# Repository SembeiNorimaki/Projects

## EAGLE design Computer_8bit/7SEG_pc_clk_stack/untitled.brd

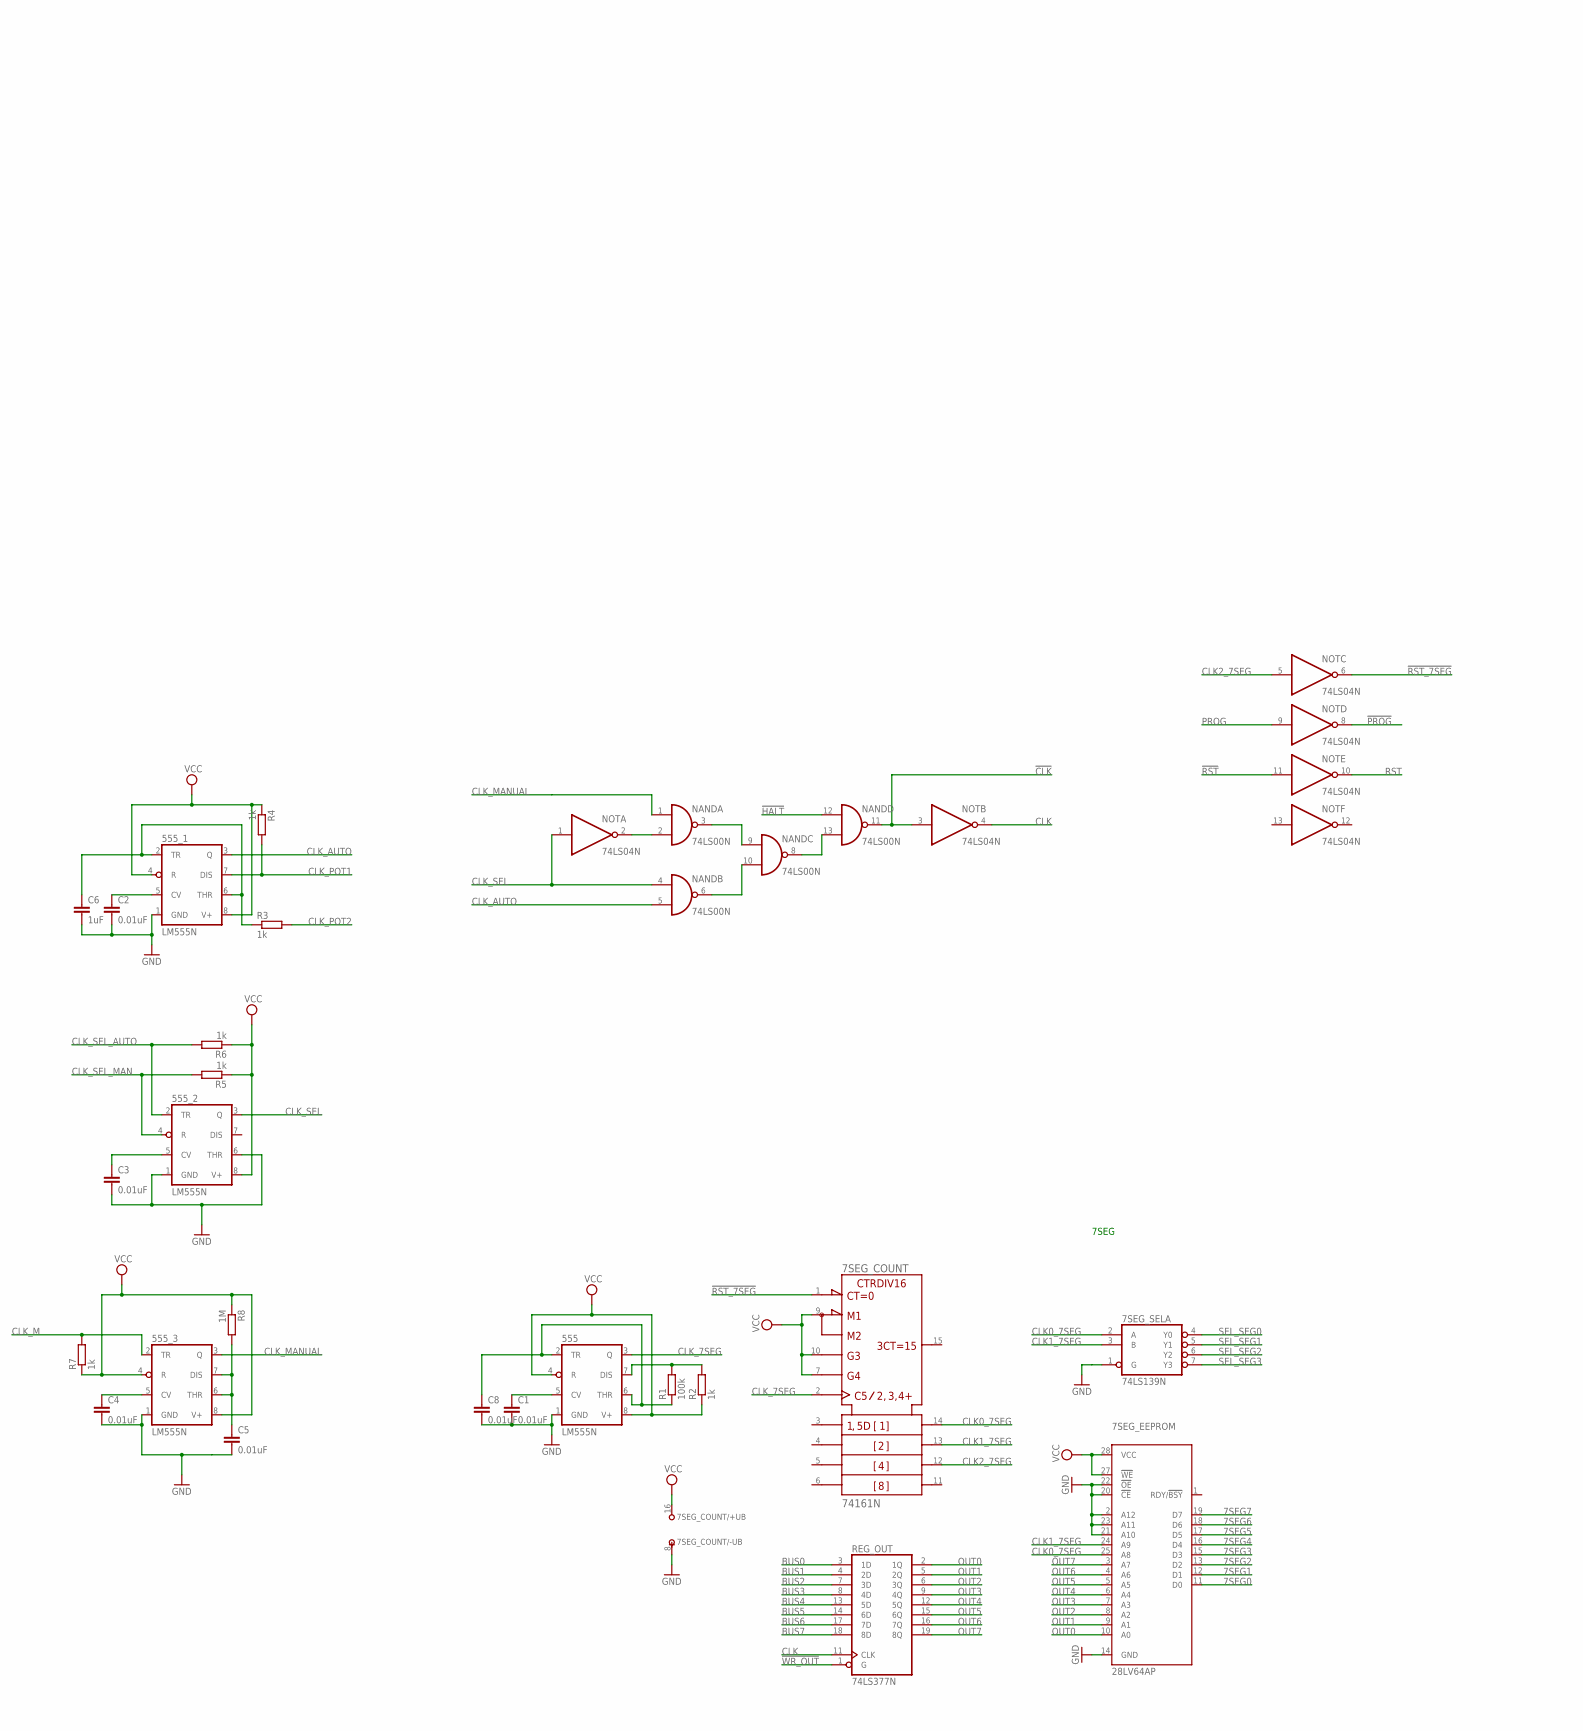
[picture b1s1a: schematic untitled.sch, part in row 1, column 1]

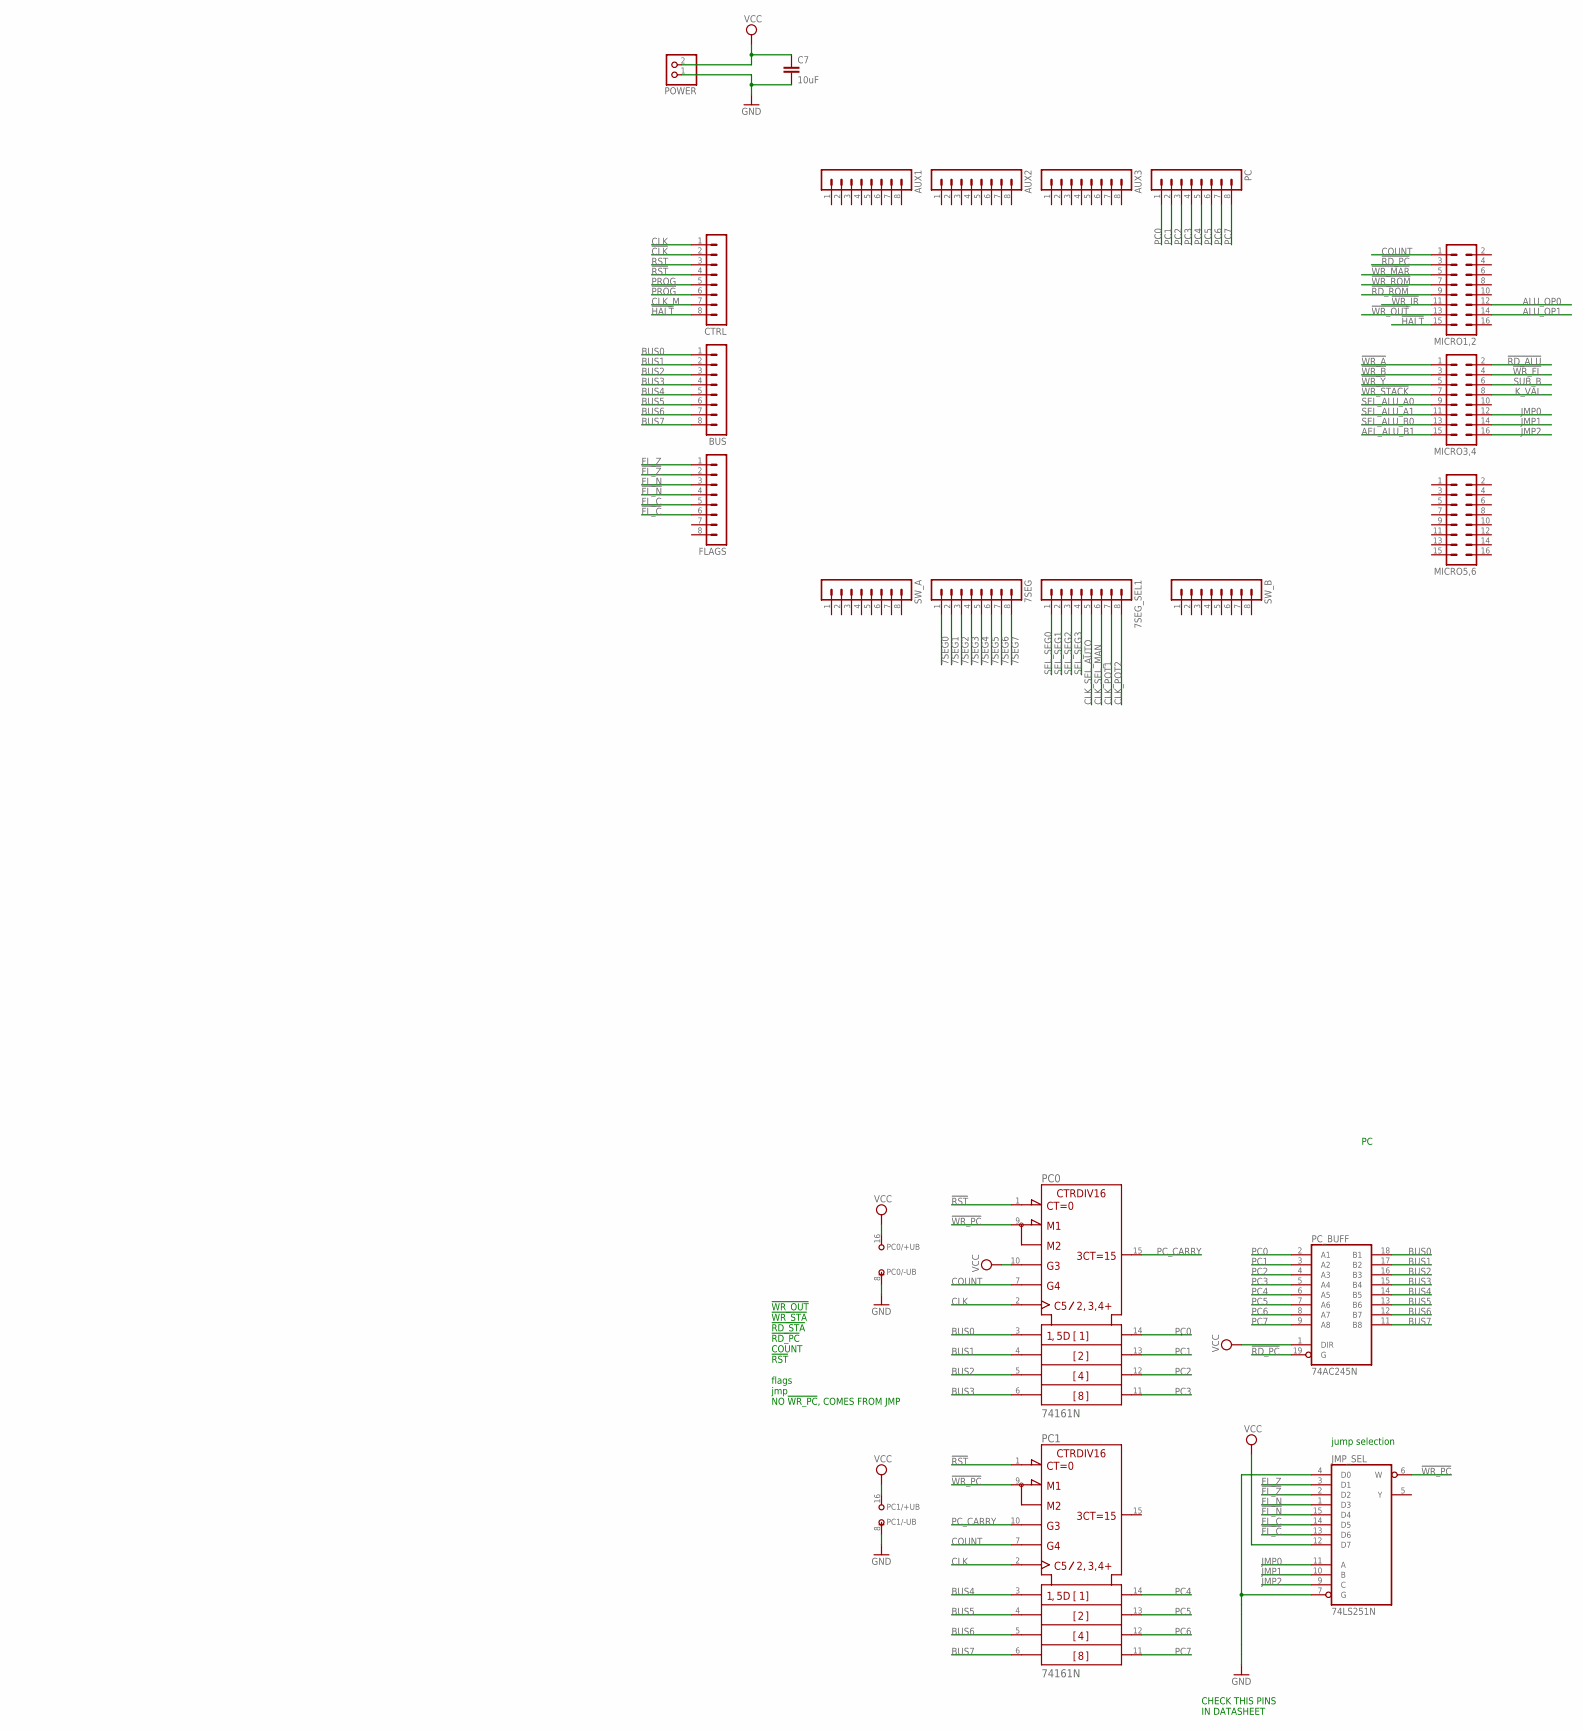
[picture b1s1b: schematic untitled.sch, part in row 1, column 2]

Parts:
7SEG, 7SEG_SEL1: MA08-1
7SEG_COUNT: 74161N; DIL16
7SEG_EEPROM: 28LV64AP; DIL28-6
7SEG_SEL: 74LS139N; DIL16
555, 555_1, 555_2, 555_3: LM555N; DIL08
AUX1, AUX2, AUX3: MA08-1
BUS: MA08-1
C1, C2, C3, C4, C5, C8: 0.01uF; C2.5-2
C6: 1uF; C2.5-2
C7: 10uF; C025-050X050
CTRL: MA08-1
FLAGS: MA08-1
JMP_SEL: 74LS251N; DIL16
MICRO1,2, MICRO3,4, MICRO5,6: MA08-2
NAND: 74LS00N; DIL14
NOT: 74LS04N; DIL14
PC: MA08-1
PC0, PC1: 74161N; DIL16
PC_BUFF: 74AC245N; DIL20
POWER: PINHD-1X2; 1X02
R1: 100k; 0207/10
R2, R3, R4, R5, R6, R7: 1k; 0207/10
R8: 1M; 0207/10
REG_OUT: 74LS377N; DIL20
SW_A: MA08-1
SW_B: MA08-1

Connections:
7SEG0: 7SEG.1, 7SEG_EEPROM.11 (D0)
7SEG1: 7SEG.2, 7SEG_EEPROM.12 (D1)
7SEG2: 7SEG.3, 7SEG_EEPROM.13 (D2)
7SEG3: 7SEG.4, 7SEG_EEPROM.15 (D3)
7SEG4: 7SEG.5, 7SEG_EEPROM.16 (D4)
7SEG5: 7SEG.6, 7SEG_EEPROM.17 (D5)
7SEG6: 7SEG.7, 7SEG_EEPROM.18 (D6)
7SEG7: 7SEG.8, 7SEG_EEPROM.19 (D7)
!CLK: CTRL.2, NAND.11 (O), NOT.3 (I)
!FL_C: FLAGS.6, JMP_SEL.13 (D6)
!FL_N: FLAGS.4, JMP_SEL.15 (D4)
!FL_Z: FLAGS.2, JMP_SEL.2 (D2)
!HALT: CTRL.8, MICRO1,2.15, NAND.12 (I0)
!PROG: CTRL.6, NOT.8 (O)
!RD_ALU: MICRO3,4.2
!RD_PC: MICRO1,2.3, PC_BUFF.19 (G)
!RD_ROM: MICRO1,2.9
!RST: CTRL.4, NOT.11 (I), PC0.1 (!CLR), PC1.1 (!CLR)
!RST_7SEG: 7SEG_COUNT.1 (!CLR), NOT.6 (O)
!WR_A: MICRO3,4.1
!WR_B: MICRO3,4.3
!WR_FL: MICRO3,4.4
!WR_IR: MICRO1,2.11
!WR_MAR: MICRO1,2.5
!WR_OUT: MICRO1,2.13, REG_OUT.1 (G)
!WR_PC: JMP_SEL.6 (W), PC0.9 (!LOAD), PC1.9 (!LOAD)
!WR_ROM: MICRO1,2.7
!WR_STACK: MICRO3,4.7
!WR_Y: MICRO3,4.5
AEL_ALU_B1: MICRO3,4.15
ALU_OP0: MICRO1,2.12
ALU_OP1: MICRO1,2.14
BUS0: BUS.1, PC0.3 (A), PC_BUFF.18 (B1), REG_OUT.3 (1D)
BUS1: BUS.2, PC0.4 (B), PC_BUFF.17 (B2), REG_OUT.4 (2D)
BUS2: BUS.3, PC0.5 (C), PC_BUFF.16 (B3), REG_OUT.7 (3D)
BUS3: BUS.4, PC0.6 (D), PC_BUFF.15 (B4), REG_OUT.8 (4D)
BUS4: BUS.5, PC1.3 (A), PC_BUFF.14 (B5), REG_OUT.13 (5D)
BUS5: BUS.6, PC1.4 (B), PC_BUFF.13 (B6), REG_OUT.14 (6D)
BUS6: BUS.7, PC1.5 (C), PC_BUFF.12 (B7), REG_OUT.17 (7D)
BUS7: BUS.8, PC1.6 (D), PC_BUFF.11 (B8), REG_OUT.18 (8D)
CLK: CTRL.1, NOT.4 (O), PC0.2 (CLK), PC1.2 (CLK), REG_OUT.11 (CLK)
CLK0_7SEG: 7SEG_COUNT.14 (QA), 7SEG_EEPROM.25 (A8), 7SEG_SEL.2 (A)
CLK1_7SEG: 7SEG_COUNT.13 (QB), 7SEG_EEPROM.24 (A9), 7SEG_SEL.3 (B)
CLK2_7SEG: 7SEG_COUNT.12 (QC), NOT.5 (I)
CLK_7SEG: 7SEG_COUNT.2 (CLK), 555.3 (Q)
CLK_AUTO: 555_1.3 (Q), NAND.5 (I1)
CLK_M: 555_3.2 (TR), CTRL.7, R7.2
CLK_MANUAL: 555_3.3 (Q), NAND.1 (I0)
CLK_POT1: 7SEG_SEL1.7, 555_1.7 (DIS), R4.2
CLK_POT2: 7SEG_SEL1.8, R3.2
CLK_SEL: 555_2.3 (Q), NAND.4 (I0), NOT.1 (I)
CLK_SEL_AUTO: 7SEG_SEL1.5, 555_2.2 (TR), R6.2
CLK_SEL_MAN: 7SEG_SEL1.6, 555_2.4 (R), R5.2
COUNT: MICRO1,2.1, PC0.7 (ENP), PC1.7 (ENP)
FL_C: FLAGS.5, JMP_SEL.14 (D5)
FL_N: FLAGS.3, JMP_SEL.1 (D3)
FL_Z: FLAGS.1, JMP_SEL.3 (D1)
GND: 7SEG_COUNT.8 (-UB), 7SEG_EEPROM.2 (A12), 7SEG_EEPROM.14 (GND), 7SEG_EEPROM.20 (!CE), 7SEG_EEPROM.21 (A10), 7SEG_EEPROM.22 (!OE), 7SEG_EEPROM.23 (A11), 7SEG_SEL.1 (G), 7SEG_SEL.8 (GND), 555.1 (GND), 555_1.1 (GND), 555_2.1 (GND), 555_2.6 (THR), 555_3.1 (GND), C1.2, C2.2, C3.2, C4.2, C5.2, C6.2, C7.2, C8.2, JMP_SEL.4 (D0), JMP_SEL.7 (G), JMP_SEL.8 (GND), NAND.7 (GND), NOT.7 (GND), PC0.8 (-UB), PC1.8 (-UB), PC_BUFF.10 (GND), POWER.1, REG_OUT.10 (GND)
JMP0: JMP_SEL.11 (A), MICRO3,4.12
JMP1: JMP_SEL.10 (B), MICRO3,4.14
JMP2: JMP_SEL.9 (C), MICRO3,4.16
K_VAL: MICRO3,4.8
unnamed: 555_2.5 (CV), C3.1
unnamed: 555_1.5 (CV), C2.1
unnamed: NAND.3 (O), NAND.9 (I0)
unnamed: 555_1.2 (TR), 555_1.6 (THR), C6.1, R3.1
unnamed: 555_3.5 (CV), C4.1
unnamed: 555.7 (DIS), R1.2, R2.2
unnamed: 555.5 (CV), C1.1
unnamed: 555.2 (TR), 555.6 (THR), C8.1, R1.1
unnamed: 555_3.6 (THR), 555_3.7 (DIS), C5.1, R8.2
unnamed: NAND.6 (O), NAND.10 (I1)
unnamed: NAND.8 (O), NAND.13 (I1)
unnamed: NAND.2 (I1), NOT.2 (O)
OUT0: 7SEG_EEPROM.10 (A0), REG_OUT.2 (1Q)
OUT1: 7SEG_EEPROM.9 (A1), REG_OUT.5 (2Q)
OUT2: 7SEG_EEPROM.8 (A2), REG_OUT.6 (3Q)
OUT3: 7SEG_EEPROM.7 (A3), REG_OUT.9 (4Q)
OUT4: 7SEG_EEPROM.6 (A4), REG_OUT.12 (5Q)
OUT5: 7SEG_EEPROM.5 (A5), REG_OUT.15 (6Q)
OUT6: 7SEG_EEPROM.4 (A6), REG_OUT.16 (7Q)
OUT7: 7SEG_EEPROM.3 (A7), REG_OUT.19 (8Q)
PC0: PC.1, PC0.14 (QA), PC_BUFF.2 (A1)
PC1: PC.2, PC0.13 (QB), PC_BUFF.3 (A2)
PC2: PC.3, PC0.12 (QC), PC_BUFF.4 (A3)
PC3: PC.4, PC0.11 (QD), PC_BUFF.5 (A4)
PC4: PC.5, PC1.14 (QA), PC_BUFF.6 (A5)
PC5: PC.6, PC1.13 (QB), PC_BUFF.7 (A6)
PC6: PC.7, PC1.12 (QC), PC_BUFF.8 (A7)
PC7: PC.8, PC1.11 (QD), PC_BUFF.9 (A8)
PC_CARRY: PC0.15 (RCO), PC1.10 (ENT)
PROG: CTRL.5, NOT.9 (I)
RST: CTRL.3, NOT.10 (O)
SEL_ALU_A0: MICRO3,4.9
SEL_ALU_A1: MICRO3,4.11
SEL_ALU_B0: MICRO3,4.13
SEL_SEG0: 7SEG_SEL.4 (Y0), 7SEG_SEL1.1
SEL_SEG1: 7SEG_SEL.5 (Y1), 7SEG_SEL1.2
SEL_SEG2: 7SEG_SEL.6 (Y2), 7SEG_SEL1.3
SEL_SEG3: 7SEG_SEL.7 (Y3), 7SEG_SEL1.4
SUB_B: MICRO3,4.6
VCC: 7SEG_COUNT.7 (ENP), 7SEG_COUNT.9 (!LOAD), 7SEG_COUNT.10 (ENT), 7SEG_COUNT.16 (+UB), 7SEG_EEPROM.27 (!WE), 7SEG_EEPROM.28 (VCC), 7SEG_SEL.16 (VCC), 555.4 (R), 555.8 (V+), 555_1.4 (R), 555_1.8 (V+), 555_2.8 (V+), 555_3.4 (R), 555_3.8 (V+), C7.1, JMP_SEL.12 (D7), JMP_SEL.16 (VCC), NAND.14 (VCC), NOT.14 (VCC), PC0.10 (ENT), PC0.16 (+UB), PC1.16 (+UB), PC_BUFF.1 (DIR), PC_BUFF.20 (VCC), POWER.2, R2.1, R4.1, R5.1, R6.1, R7.1, R8.1, REG_OUT.20 (VCC)

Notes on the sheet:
jump selection
CHECK THIS PINS IN DATASHEET
!WR_OUT !WR_STA !RD_STA !RD_PC COUNT !RST flags jmp NO !WR_PC, COMES FROM JMP
7SEG

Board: 2 copper layers, 45 parts (0 on the bottom side), 84 nets, no tracks yet.

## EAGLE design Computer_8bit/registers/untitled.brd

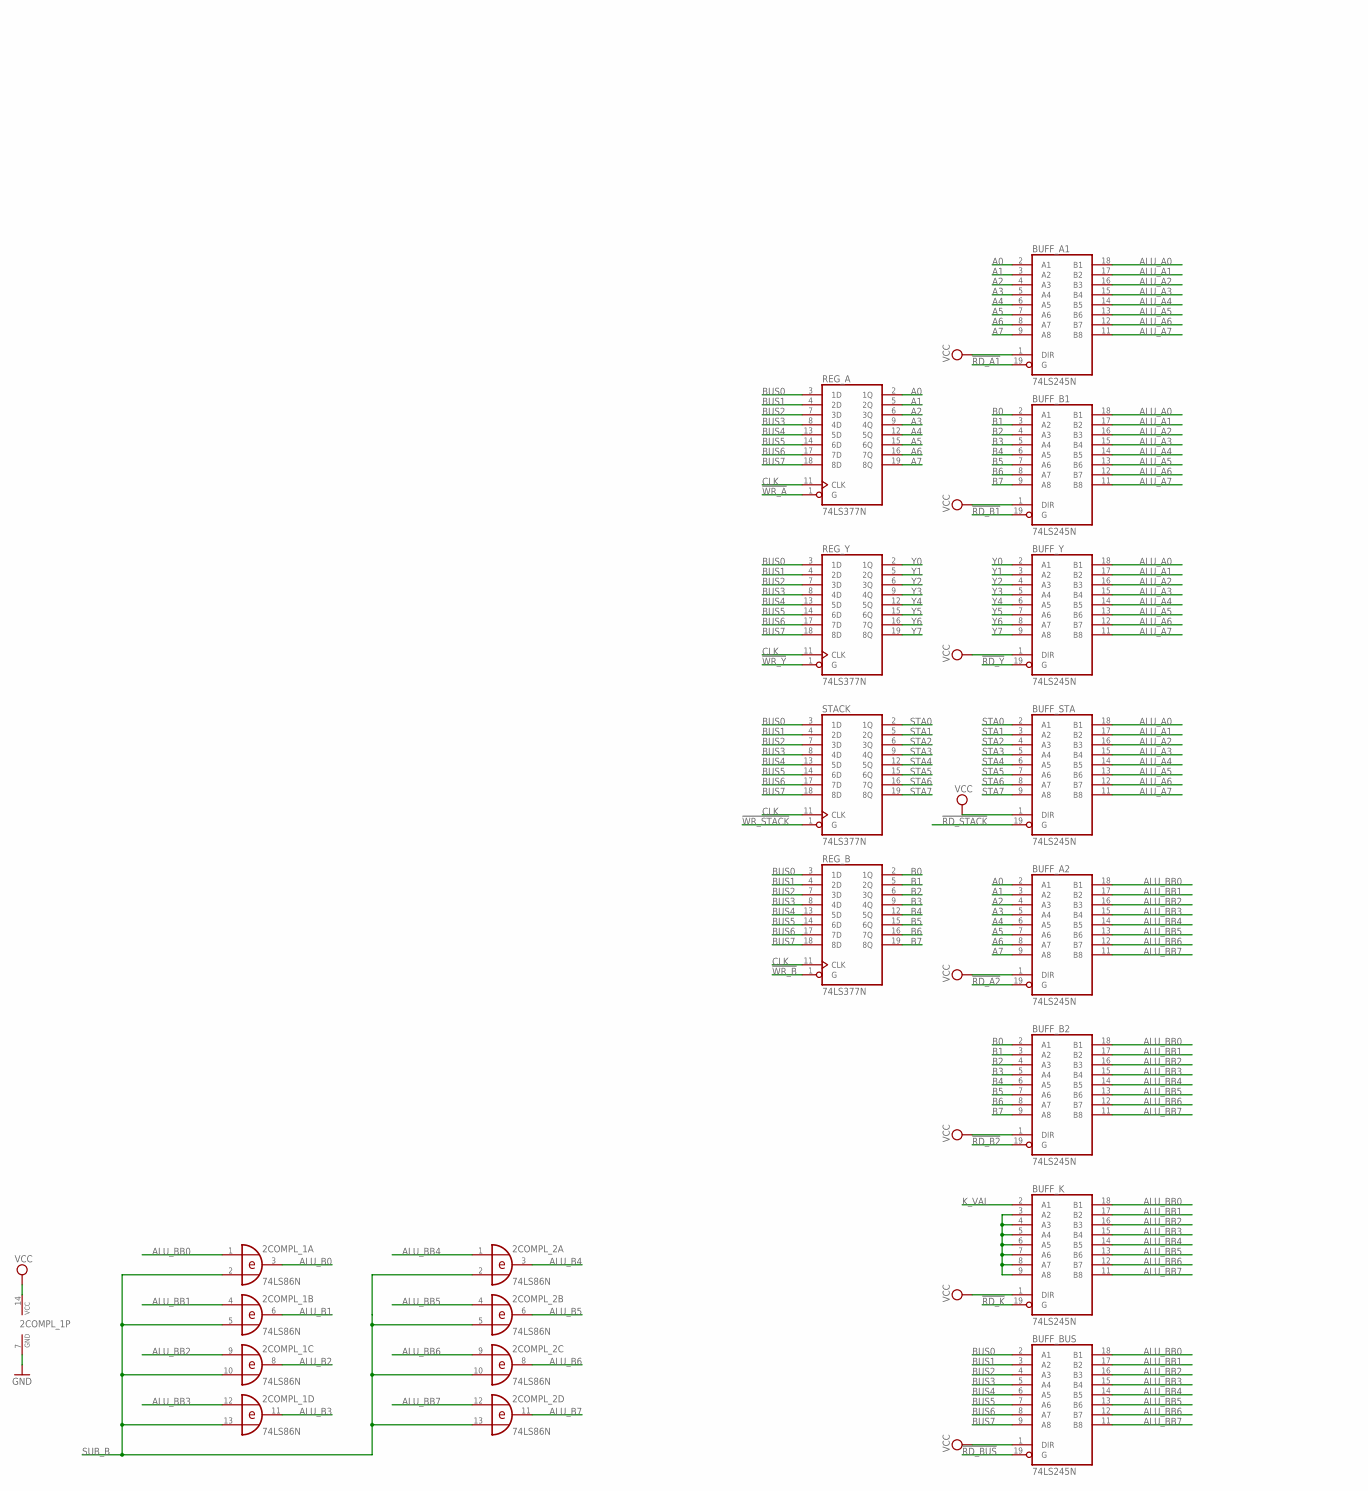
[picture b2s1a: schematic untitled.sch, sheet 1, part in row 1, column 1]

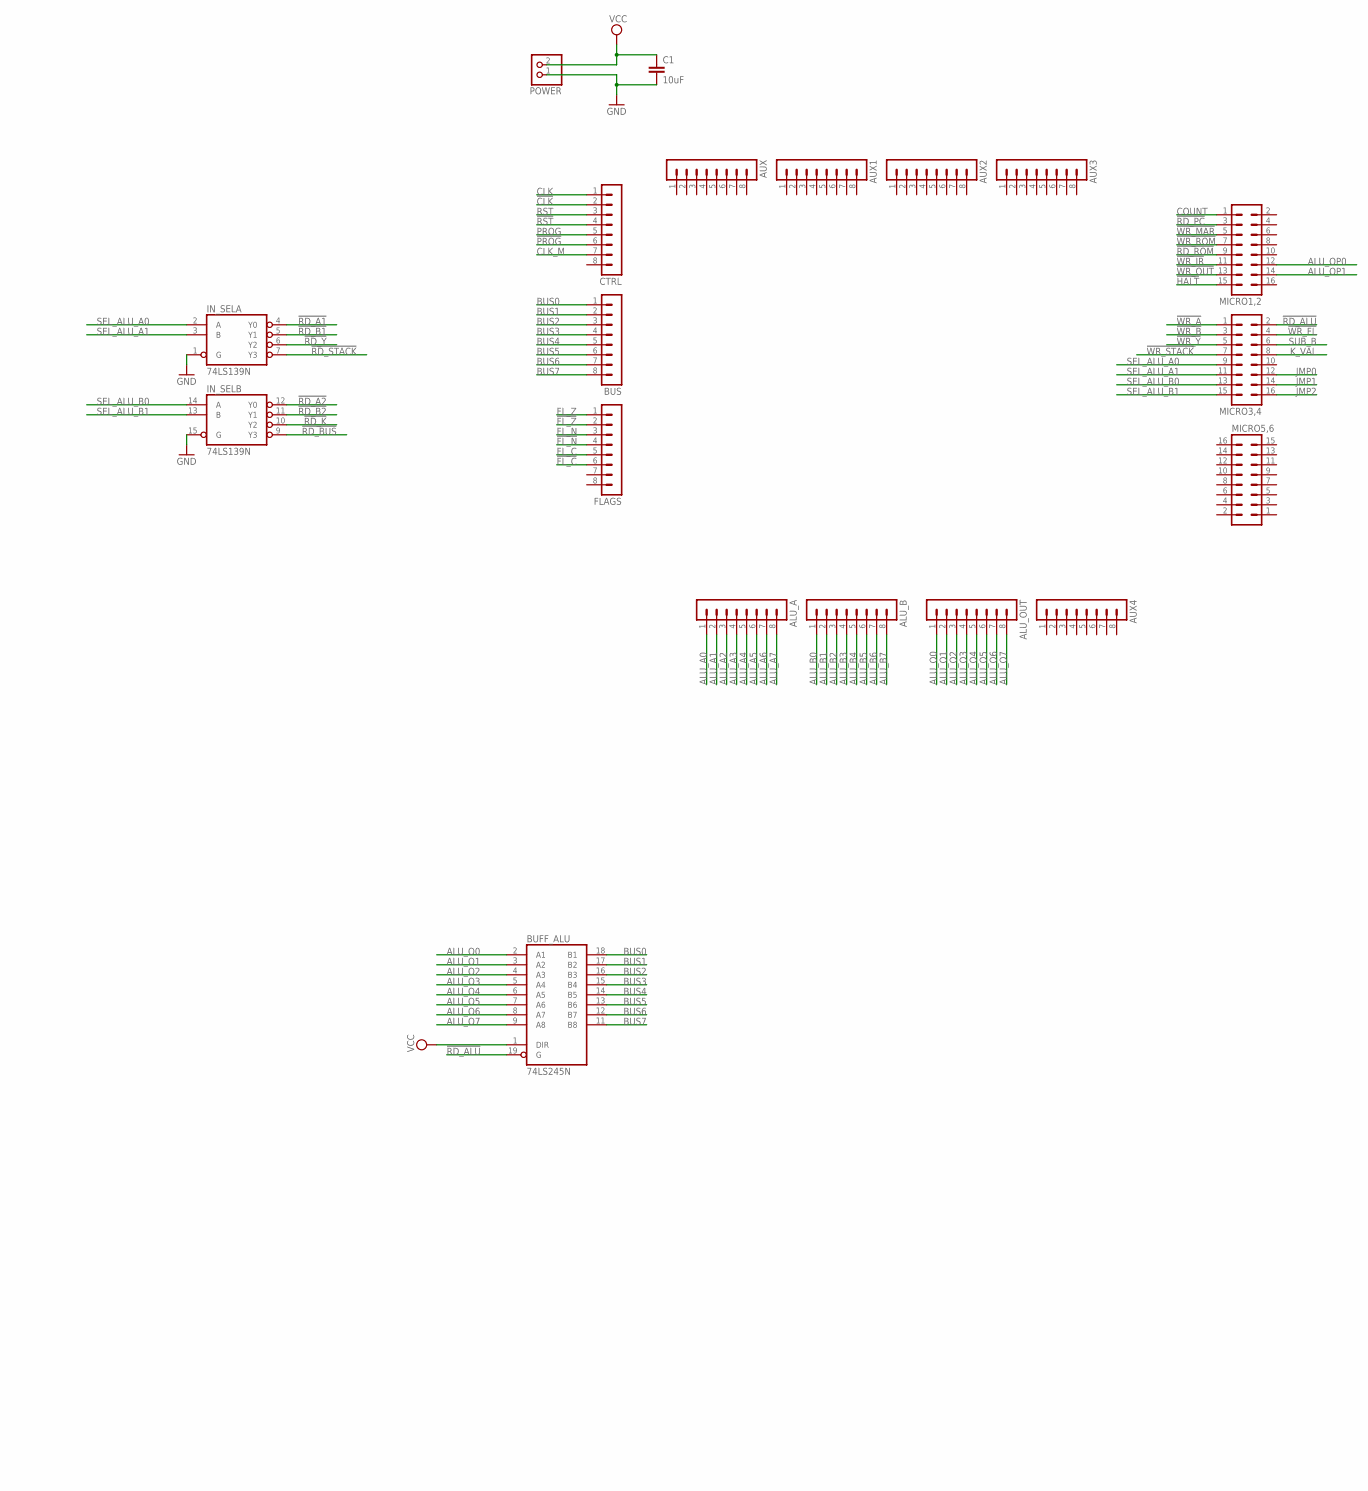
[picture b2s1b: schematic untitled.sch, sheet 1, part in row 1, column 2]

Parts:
2COMPL_1, 2COMPL_2: 74LS86N; DIL14
ALU_A: MA08-1
ALU_B: MA08-1
ALU_OUT: MA08-1
AUX, AUX1, AUX2, AUX3, AUX4: MA08-1
BUFF_A1, BUFF_A2: 74LS245N; DIL20
BUFF_ALU: 74LS245N; DIL20
BUFF_B1, BUFF_B2: 74LS245N; DIL20
BUFF_BUS: 74LS245N; DIL20
BUFF_K: 74LS245N; DIL20
BUFF_STA: 74LS245N; DIL20
BUFF_Y: 74LS245N; DIL20
BUS: MA08-1
C1: 10uF; C025-050X050
CTRL: MA08-1
FLAGS: MA08-1
IN_SEL: 74LS139N; DIL16
MICRO1,2, MICRO3,4, MICRO5,6: MA08-2
POWER: PINHD-1X2; 1X02
REG_A: 74LS377N; DIL20
REG_B: 74LS377N; DIL20
REG_Y: 74LS377N; DIL20
STACK: 74LS377N; DIL20

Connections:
!CLK: CTRL.2
!FL_C: FLAGS.6
!FL_N: FLAGS.4
!FL_Z: FLAGS.2
!HALT: MICRO1,2.15
!PROG: CTRL.6
!RD_A1: BUFF_A1.19 (G), IN_SEL.4 (Y0)
!RD_A2: BUFF_A2.19 (G), IN_SEL.12 (Y0)
!RD_ALU: BUFF_ALU.19 (G), MICRO3,4.2
!RD_B1: BUFF_B1.19 (G), IN_SEL.5 (Y1)
!RD_B2: BUFF_B2.19 (G), IN_SEL.11 (Y1)
!RD_BUS: BUFF_BUS.19 (G), IN_SEL.9 (Y3)
!RD_K: BUFF_K.19 (G), IN_SEL.10 (Y2)
!RD_PC: MICRO1,2.3
!RD_ROM: MICRO1,2.9
!RD_STACK: BUFF_STA.19 (G), IN_SEL.7 (Y3)
!RD_Y: BUFF_Y.19 (G), IN_SEL.6 (Y2)
!RST: CTRL.4
!WR_A: MICRO3,4.1, REG_A.1 (G)
!WR_B: MICRO3,4.3, REG_B.1 (G)
!WR_FL: MICRO3,4.4
!WR_IR: MICRO1,2.11
!WR_MAR: MICRO1,2.5
!WR_OUT: MICRO1,2.13
!WR_ROM: MICRO1,2.7
!WR_STACK: MICRO3,4.7, STACK.1 (G)
!WR_Y: MICRO3,4.5, REG_Y.1 (G)
A0: BUFF_A1.2 (A1), BUFF_A2.2 (A1), REG_A.2 (1Q)
A1: BUFF_A1.3 (A2), BUFF_A2.3 (A2), REG_A.5 (2Q)
A2: BUFF_A1.4 (A3), BUFF_A2.4 (A3), REG_A.6 (3Q)
A3: BUFF_A1.5 (A4), BUFF_A2.5 (A4), REG_A.9 (4Q)
A4: BUFF_A1.6 (A5), BUFF_A2.6 (A5), REG_A.12 (5Q)
A5: BUFF_A1.7 (A6), BUFF_A2.7 (A6), REG_A.15 (6Q)
A6: BUFF_A1.8 (A7), BUFF_A2.8 (A7), REG_A.16 (7Q)
A7: BUFF_A1.9 (A8), BUFF_A2.9 (A8), REG_A.19 (8Q)
ALU_A0: ALU_A.1, BUFF_A1.18 (B1), BUFF_B1.18 (B1), BUFF_STA.18 (B1), BUFF_Y.18 (B1)
ALU_A1: ALU_A.2, BUFF_A1.17 (B2), BUFF_B1.17 (B2), BUFF_STA.17 (B2), BUFF_Y.17 (B2)
ALU_A2: ALU_A.3, BUFF_A1.16 (B3), BUFF_B1.16 (B3), BUFF_STA.16 (B3), BUFF_Y.16 (B3)
ALU_A3: ALU_A.4, BUFF_A1.15 (B4), BUFF_B1.15 (B4), BUFF_STA.15 (B4), BUFF_Y.15 (B4)
ALU_A4: ALU_A.5, BUFF_A1.14 (B5), BUFF_B1.14 (B5), BUFF_STA.14 (B5), BUFF_Y.14 (B5)
ALU_A5: ALU_A.6, BUFF_A1.13 (B6), BUFF_B1.13 (B6), BUFF_STA.13 (B6), BUFF_Y.13 (B6)
ALU_A6: ALU_A.7, BUFF_A1.12 (B7), BUFF_B1.12 (B7), BUFF_STA.12 (B7), BUFF_Y.12 (B7)
ALU_A7: ALU_A.8, BUFF_A1.11 (B8), BUFF_B1.11 (B8), BUFF_STA.11 (B8), BUFF_Y.11 (B8)
ALU_B0: 2COMPL_1.3 (O), ALU_B.1
ALU_B1: 2COMPL_1.6 (O), ALU_B.2
ALU_B2: 2COMPL_1.8 (O), ALU_B.3
ALU_B3: 2COMPL_1.11 (O), ALU_B.4
ALU_B4: 2COMPL_2.3 (O), ALU_B.5
ALU_B5: 2COMPL_2.6 (O), ALU_B.6
ALU_B6: 2COMPL_2.8 (O), ALU_B.7
ALU_B7: 2COMPL_2.11 (O), ALU_B.8
ALU_BB0: 2COMPL_1.1 (I0), BUFF_A2.18 (B1), BUFF_B2.18 (B1), BUFF_BUS.18 (B1), BUFF_K.18 (B1)
ALU_BB1: 2COMPL_1.4 (I0), BUFF_A2.17 (B2), BUFF_B2.17 (B2), BUFF_BUS.17 (B2), BUFF_K.17 (B2)
ALU_BB2: 2COMPL_1.9 (I0), BUFF_A2.16 (B3), BUFF_B2.16 (B3), BUFF_BUS.16 (B3), BUFF_K.16 (B3)
ALU_BB3: 2COMPL_1.12 (I0), BUFF_A2.15 (B4), BUFF_B2.15 (B4), BUFF_BUS.15 (B4), BUFF_K.15 (B4)
ALU_BB4: 2COMPL_2.1 (I0), BUFF_A2.14 (B5), BUFF_B2.14 (B5), BUFF_BUS.14 (B5), BUFF_K.14 (B5)
ALU_BB5: 2COMPL_2.4 (I0), BUFF_A2.13 (B6), BUFF_B2.13 (B6), BUFF_BUS.13 (B6), BUFF_K.13 (B6)
ALU_BB6: 2COMPL_2.9 (I0), BUFF_A2.12 (B7), BUFF_B2.12 (B7), BUFF_BUS.12 (B7), BUFF_K.12 (B7)
ALU_BB7: 2COMPL_2.12 (I0), BUFF_A2.11 (B8), BUFF_B2.11 (B8), BUFF_BUS.11 (B8), BUFF_K.11 (B8)
ALU_O0: ALU_OUT.1, BUFF_ALU.2 (A1)
ALU_O1: ALU_OUT.2, BUFF_ALU.3 (A2)
ALU_O2: ALU_OUT.3, BUFF_ALU.4 (A3)
ALU_O3: ALU_OUT.4, BUFF_ALU.5 (A4)
ALU_O4: ALU_OUT.5, BUFF_ALU.6 (A5)
ALU_O5: ALU_OUT.6, BUFF_ALU.7 (A6)
ALU_O6: ALU_OUT.7, BUFF_ALU.8 (A7)
ALU_O7: ALU_OUT.8, BUFF_ALU.9 (A8)
ALU_OP0: MICRO1,2.12
ALU_OP1: MICRO1,2.14
B0: BUFF_B1.2 (A1), BUFF_B2.2 (A1), REG_B.2 (1Q)
B1: BUFF_B1.3 (A2), BUFF_B2.3 (A2), REG_B.5 (2Q)
B2: BUFF_B1.4 (A3), BUFF_B2.4 (A3), REG_B.6 (3Q)
B3: BUFF_B1.5 (A4), BUFF_B2.5 (A4), REG_B.9 (4Q)
B4: BUFF_B1.6 (A5), BUFF_B2.6 (A5), REG_B.12 (5Q)
B5: BUFF_B1.7 (A6), BUFF_B2.7 (A6), REG_B.15 (6Q)
B6: BUFF_B1.8 (A7), BUFF_B2.8 (A7), REG_B.16 (7Q)
B7: BUFF_B1.9 (A8), BUFF_B2.9 (A8), REG_B.19 (8Q)
BUS0: BUFF_ALU.18 (B1), BUFF_BUS.2 (A1), BUS.1, REG_A.3 (1D), REG_B.3 (1D), REG_Y.3 (1D), STACK.3 (1D)
BUS1: BUFF_ALU.17 (B2), BUFF_BUS.3 (A2), BUS.2, REG_A.4 (2D), REG_B.4 (2D), REG_Y.4 (2D), STACK.4 (2D)
BUS2: BUFF_ALU.16 (B3), BUFF_BUS.4 (A3), BUS.3, REG_A.7 (3D), REG_B.7 (3D), REG_Y.7 (3D), STACK.7 (3D)
BUS3: BUFF_ALU.15 (B4), BUFF_BUS.5 (A4), BUS.4, REG_A.8 (4D), REG_B.8 (4D), REG_Y.8 (4D), STACK.8 (4D)
BUS4: BUFF_ALU.14 (B5), BUFF_BUS.6 (A5), BUS.5, REG_A.13 (5D), REG_B.13 (5D), REG_Y.13 (5D), STACK.13 (5D)
BUS5: BUFF_ALU.13 (B6), BUFF_BUS.7 (A6), BUS.6, REG_A.14 (6D), REG_B.14 (6D), REG_Y.14 (6D), STACK.14 (6D)
BUS6: BUFF_ALU.12 (B7), BUFF_BUS.8 (A7), BUS.7, REG_A.17 (7D), REG_B.17 (7D), REG_Y.17 (7D), STACK.17 (7D)
BUS7: BUFF_ALU.11 (B8), BUFF_BUS.9 (A8), BUS.8, REG_A.18 (8D), REG_B.18 (8D), REG_Y.18 (8D), STACK.18 (8D)
CLK: CTRL.1, REG_A.11 (CLK), REG_B.11 (CLK), REG_Y.11 (CLK), STACK.11 (CLK)
CLK_M: CTRL.7
COUNT: MICRO1,2.1
FL_C: FLAGS.5
FL_N: FLAGS.3
FL_Z: FLAGS.1
GND: 2COMPL_1.7 (GND), 2COMPL_2.7 (GND), BUFF_A1.10 (GND), BUFF_A2.10 (GND), BUFF_ALU.10 (GND), BUFF_B1.10 (GND), BUFF_B2.10 (GND), BUFF_BUS.10 (GND), BUFF_K.10 (GND), BUFF_STA.10 (GND), BUFF_Y.10 (GND), C1.2, IN_SEL.1 (G), IN_SEL.8 (GND), IN_SEL.15 (G), POWER.1, REG_A.10 (GND), REG_B.10 (GND), REG_Y.10 (GND), STACK.10 (GND)
JMP0: MICRO3,4.12
JMP1: MICRO3,4.14
JMP2: MICRO3,4.16
K_VAL: BUFF_K.2 (A1), MICRO3,4.8
unnamed: BUFF_K.3 (A2), BUFF_K.4 (A3), BUFF_K.5 (A4), BUFF_K.6 (A5), BUFF_K.7 (A6), BUFF_K.8 (A7), BUFF_K.9 (A8)
PROG: CTRL.5
RST: CTRL.3
SEL_ALU_A0: IN_SEL.2 (A), MICRO3,4.9
SEL_ALU_A1: IN_SEL.3 (B), MICRO3,4.11
SEL_ALU_B0: IN_SEL.14 (A), MICRO3,4.13
SEL_ALU_B1: IN_SEL.13 (B), MICRO3,4.15
STA0: BUFF_STA.2 (A1), STACK.2 (1Q)
STA1: BUFF_STA.3 (A2), STACK.5 (2Q)
STA2: BUFF_STA.4 (A3), STACK.6 (3Q)
STA3: BUFF_STA.5 (A4), STACK.9 (4Q)
STA4: BUFF_STA.6 (A5), STACK.12 (5Q)
STA5: BUFF_STA.7 (A6), STACK.15 (6Q)
STA6: BUFF_STA.8 (A7), STACK.16 (7Q)
STA7: BUFF_STA.9 (A8), STACK.19 (8Q)
SUB_B: 2COMPL_1.2 (I1), 2COMPL_1.5 (I1), 2COMPL_1.10 (I1), 2COMPL_1.13 (I1), 2COMPL_2.2 (I1), 2COMPL_2.5 (I1), 2COMPL_2.10 (I1), 2COMPL_2.13 (I1), MICRO3,4.6
VCC: 2COMPL_1.14 (VCC), 2COMPL_2.14 (VCC), BUFF_A1.1 (DIR), BUFF_A1.20 (VCC), BUFF_A2.1 (DIR), BUFF_A2.20 (VCC), BUFF_ALU.1 (DIR), BUFF_ALU.20 (VCC), BUFF_B1.1 (DIR), BUFF_B1.20 (VCC), BUFF_B2.1 (DIR), BUFF_B2.20 (VCC), BUFF_BUS.1 (DIR), BUFF_BUS.20 (VCC), BUFF_K.1 (DIR), BUFF_K.20 (VCC), BUFF_STA.1 (DIR), BUFF_STA.20 (VCC), BUFF_Y.1 (DIR), BUFF_Y.20 (VCC), C1.1, IN_SEL.16 (VCC), POWER.2, REG_A.20 (VCC), REG_B.20 (VCC), REG_Y.20 (VCC), STACK.20 (VCC)
Y0: BUFF_Y.2 (A1), REG_Y.2 (1Q)
Y1: BUFF_Y.3 (A2), REG_Y.5 (2Q)
Y2: BUFF_Y.4 (A3), REG_Y.6 (3Q)
Y3: BUFF_Y.5 (A4), REG_Y.9 (4Q)
Y4: BUFF_Y.6 (A5), REG_Y.12 (5Q)
Y5: BUFF_Y.7 (A6), REG_Y.15 (6Q)
Y6: BUFF_Y.8 (A7), REG_Y.16 (7Q)
Y7: BUFF_Y.9 (A8), REG_Y.19 (8Q)

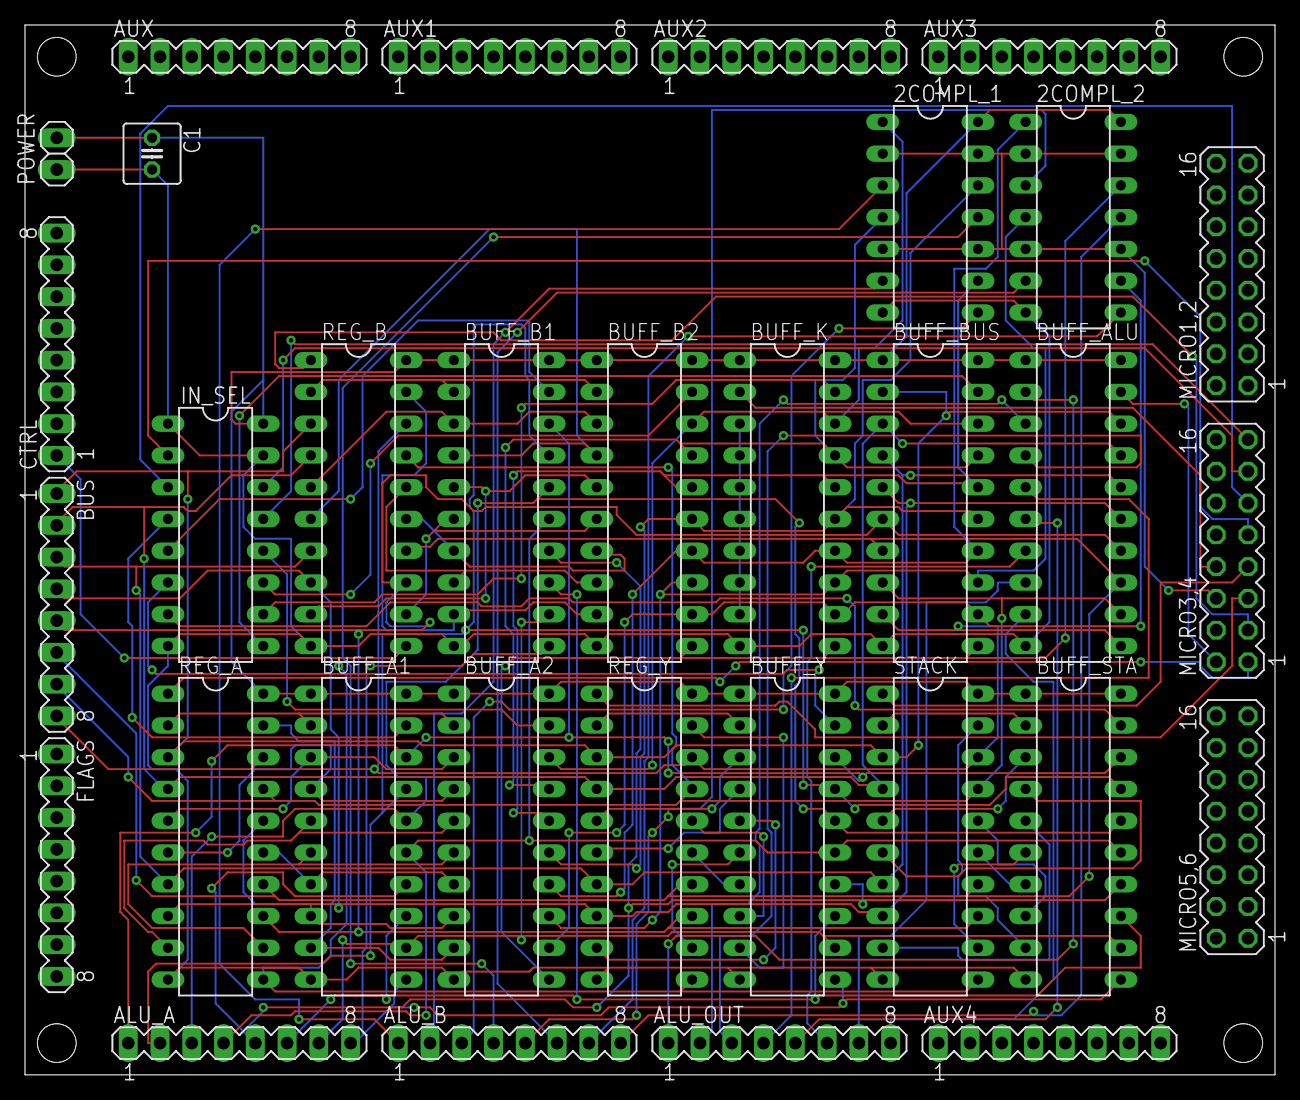
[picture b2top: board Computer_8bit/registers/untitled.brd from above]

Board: 2 copper layers, 99.9 x 83.9 mm, 32 parts (0 on the bottom side), 95 nets.
